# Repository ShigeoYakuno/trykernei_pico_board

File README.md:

# ベースボード

## 方針
- カバーなどが安く買え、種類も豊富なためラズパイ4Bサイズで作る。
- 40pinのコネクタ、M2.5サイズのホールもそのまま採用
- プログラム変更をSDカード経由で行いたいため、カードスロットを標準搭載する
- 3.7Vリポバッテリーでも起動できるよう構成する

### 全体

### 表面

### 裏面

## 3D正面

## 3D裏面

## BOM

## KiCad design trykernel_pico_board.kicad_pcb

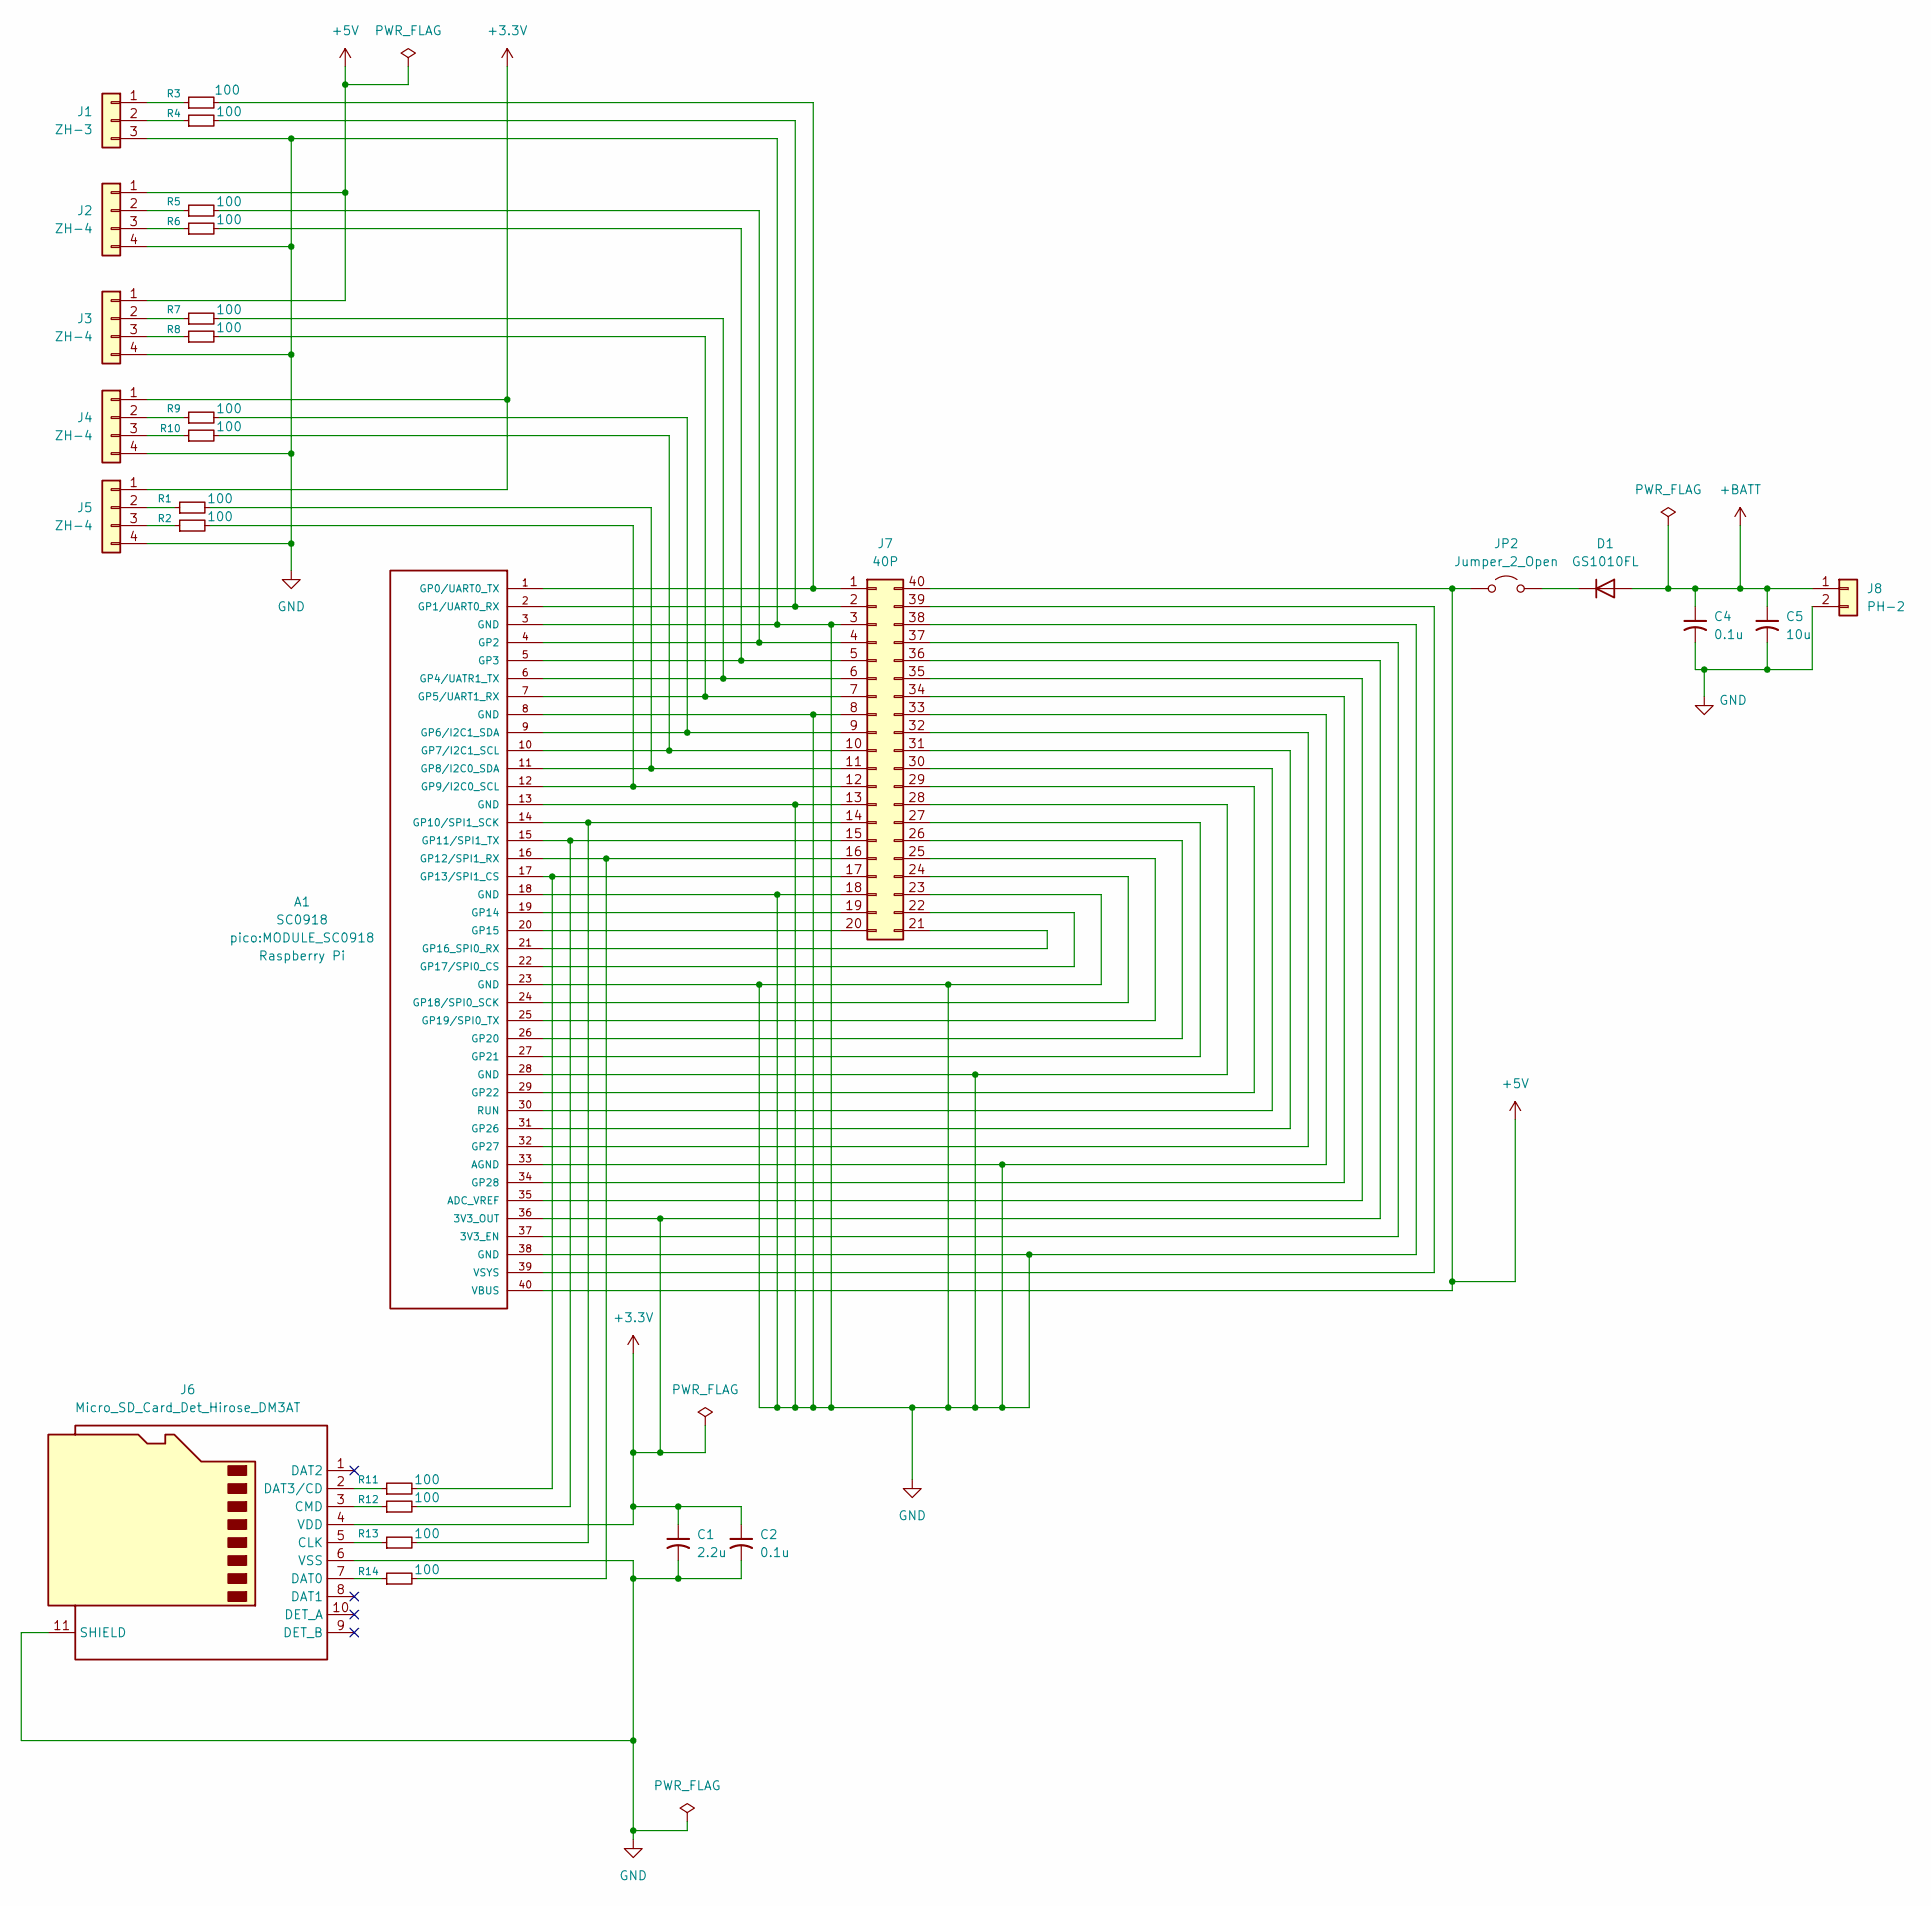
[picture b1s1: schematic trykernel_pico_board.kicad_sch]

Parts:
A1: SC0918; MODULE_SC0918; PARTREV 1.6
C1: 2.2u; C_0603_1608Metric_Pad1.08x0.95mm_HandSolder
C2: 0.1u; C_0603_1608Metric_Pad1.08x0.95mm_HandSolder
C4: 0.1u; C_0805_2012Metric_Pad1.18x1.45mm_HandSolder
C5: 10u; C_0805_2012Metric_Pad1.18x1.45mm_HandSolder
D1: GS1010FL; D_SOD-123
J1: ZH-3; JST_ZH_B3B-ZR_1x03_P1.50mm_Vertical
J2, J3, J4, J5: ZH-4; JST_ZH_B4B-ZR_1x04_P1.50mm_Vertical
J6: Micro_SD_Card_Det_Hirose_DM3AT; microSD_HC_Hirose_DM3AT-SF-PEJM5
J7: 40P; RPI_Hat_B+
J8: PH-2; JST_PH_B2B-PH-K_1x02_P2.00mm_Vertical
JP2: Jumper_2_Open; Pin_Header_Straight_1x02
R1, R2, R3, R4, R5, R6, R7, R8, R9, R10, R11, R12, R13, R14: 100; R_0603_1608Metric_Pad0.98x0.95mm_HandSolder

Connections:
+3.3V: A1.36 (3V3_OUT), C1.1, C2.1, J4.1, J5.1, J6.4 (VDD), J7.36
+5V: A1.40 (VBUS), J2.1, J3.1, J7.40, JP2.1 (A)
+BATT: C4.1, C5.1, D1.2 (A), J8.1
GND: A1.3 (GND), A1.8 (GND), A1.13 (GND), A1.18 (GND), A1.23 (GND), A1.28 (GND), A1.33 (AGND), A1.38 (GND), C1.2, C2.2, C4.2, C5.2, J1.3, J2.4, J3.4, J4.4, J5.4, J6.6 (VSS), J6.11 (SHIELD), J7.3, J7.8, J7.13, J7.18, J7.23, J7.28, J7.33, J7.38, J8.2
unnamed: A1.37 (3V3_EN), J7.37
unnamed: A1.35 (ADC_VREF), J7.35
unnamed: A1.1 (GP0/UART0_TX), J7.1, R3.2
unnamed: A1.2 (GP1/UART0_RX), J7.2, R4.2
unnamed: A1.4 (GP2), J7.4, R5.2
unnamed: A1.5 (GP3), J7.5, R6.2
unnamed: A1.6 (GP4/UATR1_TX), J7.6, R7.2
unnamed: A1.7 (GP5/UART1_RX), J7.7, R8.2
unnamed: A1.9 (GP6/I2C1_SDA), J7.9, R9.2
unnamed: A1.10 (GP7/I2C1_SCL), J7.10, R10.2
unnamed: A1.11 (GP8/I2C0_SDA), J7.11, R1.2
unnamed: A1.12 (GP9/I2C0_SCL), J7.12, R2.2
unnamed: A1.14 (GP10/SPI1_SCK), J7.14, R13.2
unnamed: A1.15 (GP11/SPI1_TX), J7.15, R12.2
unnamed: A1.16 (GP12/SPI1_RX), J7.16, R14.2
unnamed: A1.17 (GP13/SPI1_CS), J7.17, R11.2
unnamed: A1.19 (GP14), J7.19
unnamed: A1.20 (GP15), J7.20
unnamed: A1.21 (GP16_SPI0_RX), J7.21
unnamed: A1.22 (GP17/SPI0_CS), J7.22
unnamed: A1.24 (GP18/SPI0_SCK), J7.24
unnamed: A1.25 (GP19/SPI0_TX), J7.25
unnamed: A1.26 (GP20), J7.26
unnamed: A1.27 (GP21), J7.27
unnamed: A1.29 (GP22), J7.29
unnamed: A1.31 (GP26), J7.31
unnamed: A1.32 (GP27), J7.32
unnamed: A1.34 (GP28), J7.34
unnamed: A1.30 (RUN), J7.30
unnamed: A1.39 (VSYS), J7.39
unnamed: D1.1 (K), JP2.2 (B)
unnamed: J1.1, R3.1
unnamed: J1.2, R4.1
unnamed: J2.2, R5.1
unnamed: J2.3, R6.1
unnamed: J3.2, R7.1
unnamed: J3.3, R8.1
unnamed: J4.2, R9.1
unnamed: J4.3, R10.1
unnamed: J5.2, R1.1
unnamed: J5.3, R2.1
unnamed: J6.5 (CLK), R13.1
unnamed: J6.3 (CMD), R12.1
unnamed: J6.7 (DAT0), R14.1
unnamed: J6.2 (DAT3/CD), R11.1

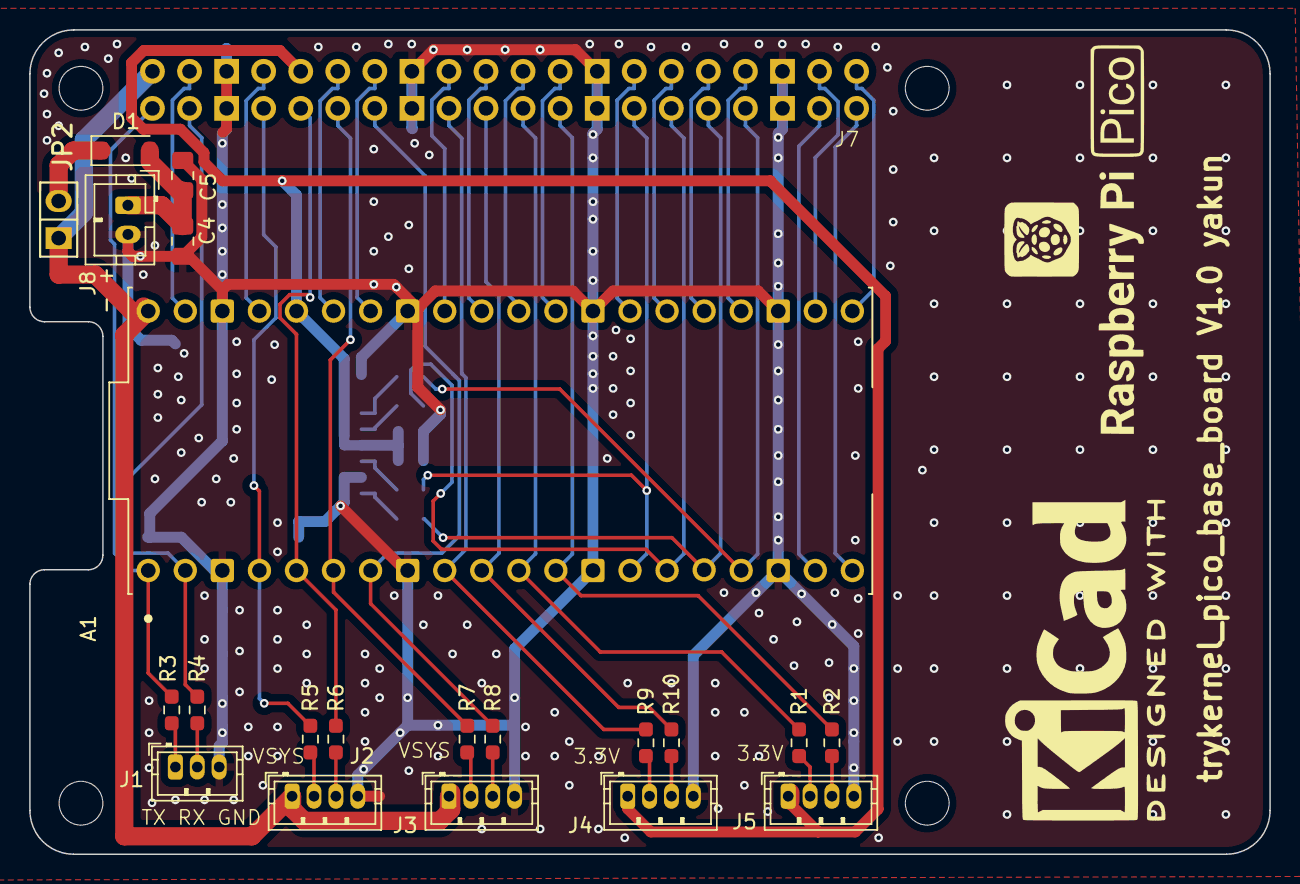
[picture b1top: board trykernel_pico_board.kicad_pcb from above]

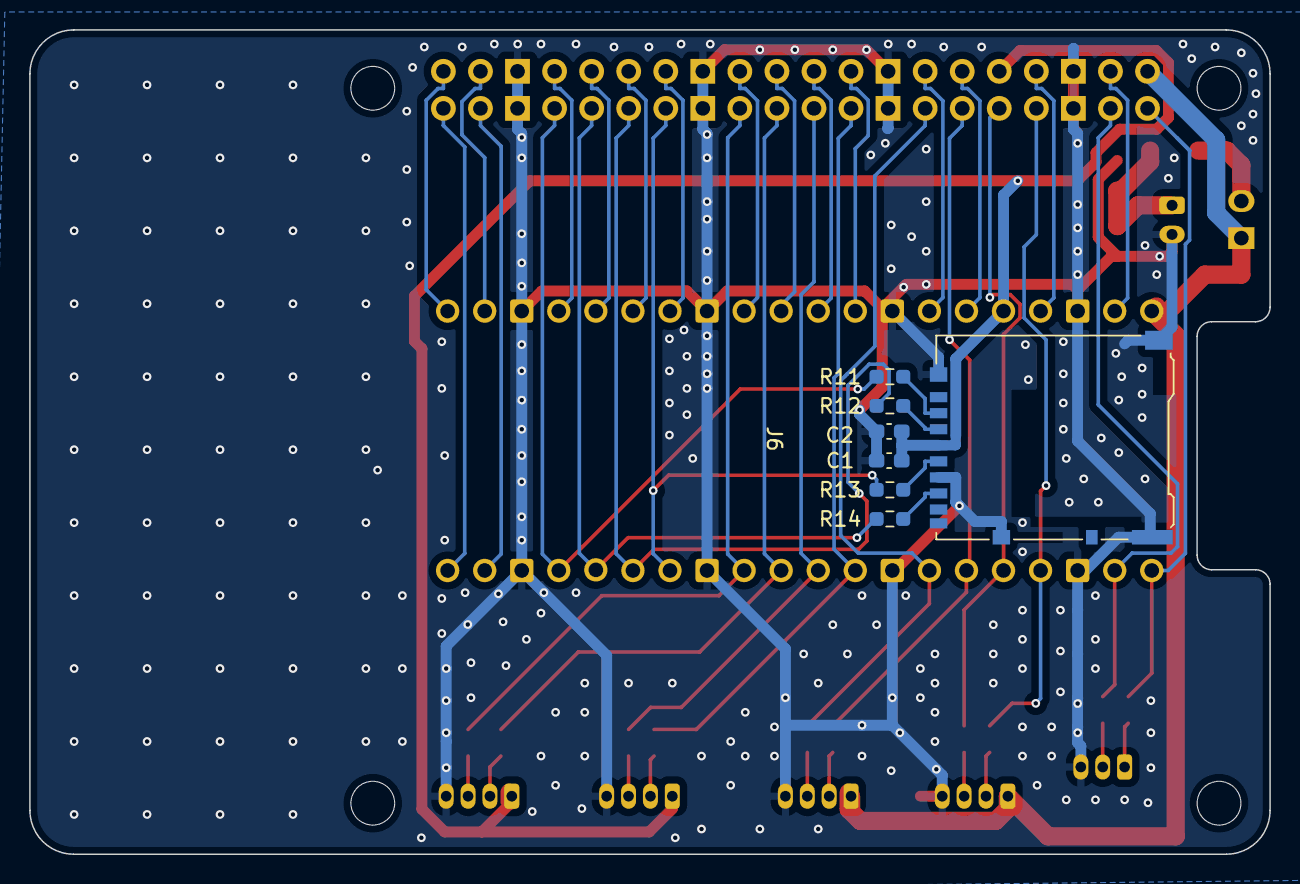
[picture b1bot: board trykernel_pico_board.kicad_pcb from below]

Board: 2 copper layers, 85.0 x 56.5 mm, 29 parts (7 on the bottom side), 49 nets.

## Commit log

2025-05-01 空プロジェクトをあげただけ
2025-05-01 ベース基板とpicoを追加
2025-05-14 version1.0 発注したもの
